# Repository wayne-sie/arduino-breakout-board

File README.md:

# arduino-breakout-board
R3 Hardware project - breakout board interfacing arduino due and adafruit ethernet featherwing 
Designed with EAGLE

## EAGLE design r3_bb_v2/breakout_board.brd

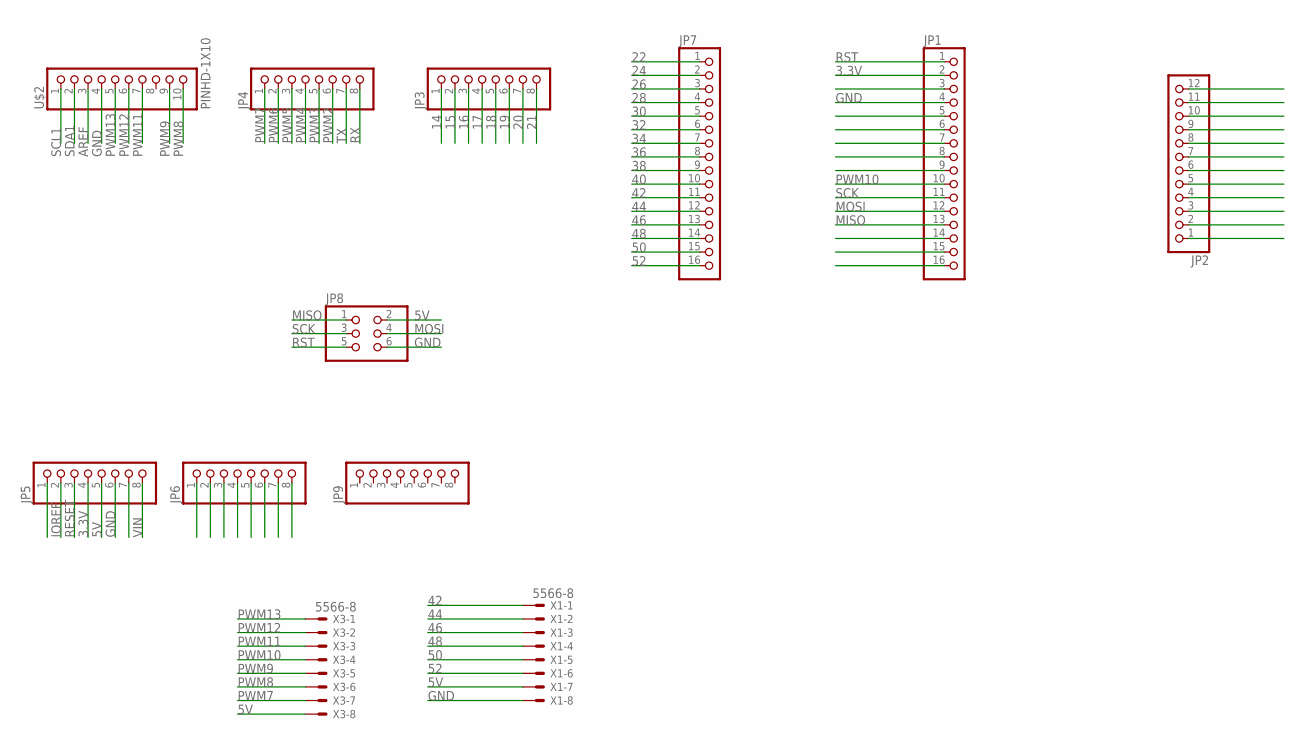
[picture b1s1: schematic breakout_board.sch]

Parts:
JP1, JP7: PINHD-1X16; 1X16
JP2: PINHD-1X12; 1X12
JP3, JP4, JP5, JP6, JP9: PINHD-1X8BIG; 1X08-BIG
JP8: PINHD-2X3; 2X03
U$2: PINHD-1X10; 1X10-BIG
X1, X3: 5566-8

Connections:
3.3V: JP1.2, JP5.4
5V: JP5.5, JP8.2, X1.7, X3.8
14: JP3.1
15: JP3.2
16: JP3.3
17: JP3.4
18: JP3.5
19: JP3.6
20: JP3.7
21: JP3.8
22: JP7.1
24: JP7.2
26: JP7.3
28: JP7.4
30: JP7.5
32: JP7.6
34: JP7.7
36: JP7.8
38: JP7.9
40: JP7.10
42: JP7.11, X1.1
44: JP7.12, X1.2
46: JP7.13, X1.3
48: JP7.14, X1.4
50: JP7.15, X1.5
52: JP7.16, X1.6
AREF: U$2.3
GND: JP1.4, JP5.6, JP8.6, U$2.4, X1.8
IOREF: JP5.2
MISO: JP1.13, JP8.1
MOSI: JP1.12, JP8.4
PWM2: JP4.6
PWM3: JP4.5
PWM4: JP4.4
PWM5: JP4.3
PWM6: JP4.2
PWM7: JP4.1, X3.7
PWM8: U$2.10, X3.6
PWM9: U$2.9, X3.5
PWM10: JP1.10, X3.4
PWM11: U$2.7, X3.3
PWM12: U$2.6, X3.2
PWM13: U$2.5, X3.1
RESET: JP5.3
RST: JP1.1, JP8.5
RX: JP4.8
SCK: JP1.11, JP8.3
SCL1: U$2.1
SDA1: U$2.2
TX: JP4.7
VIN: JP5.8

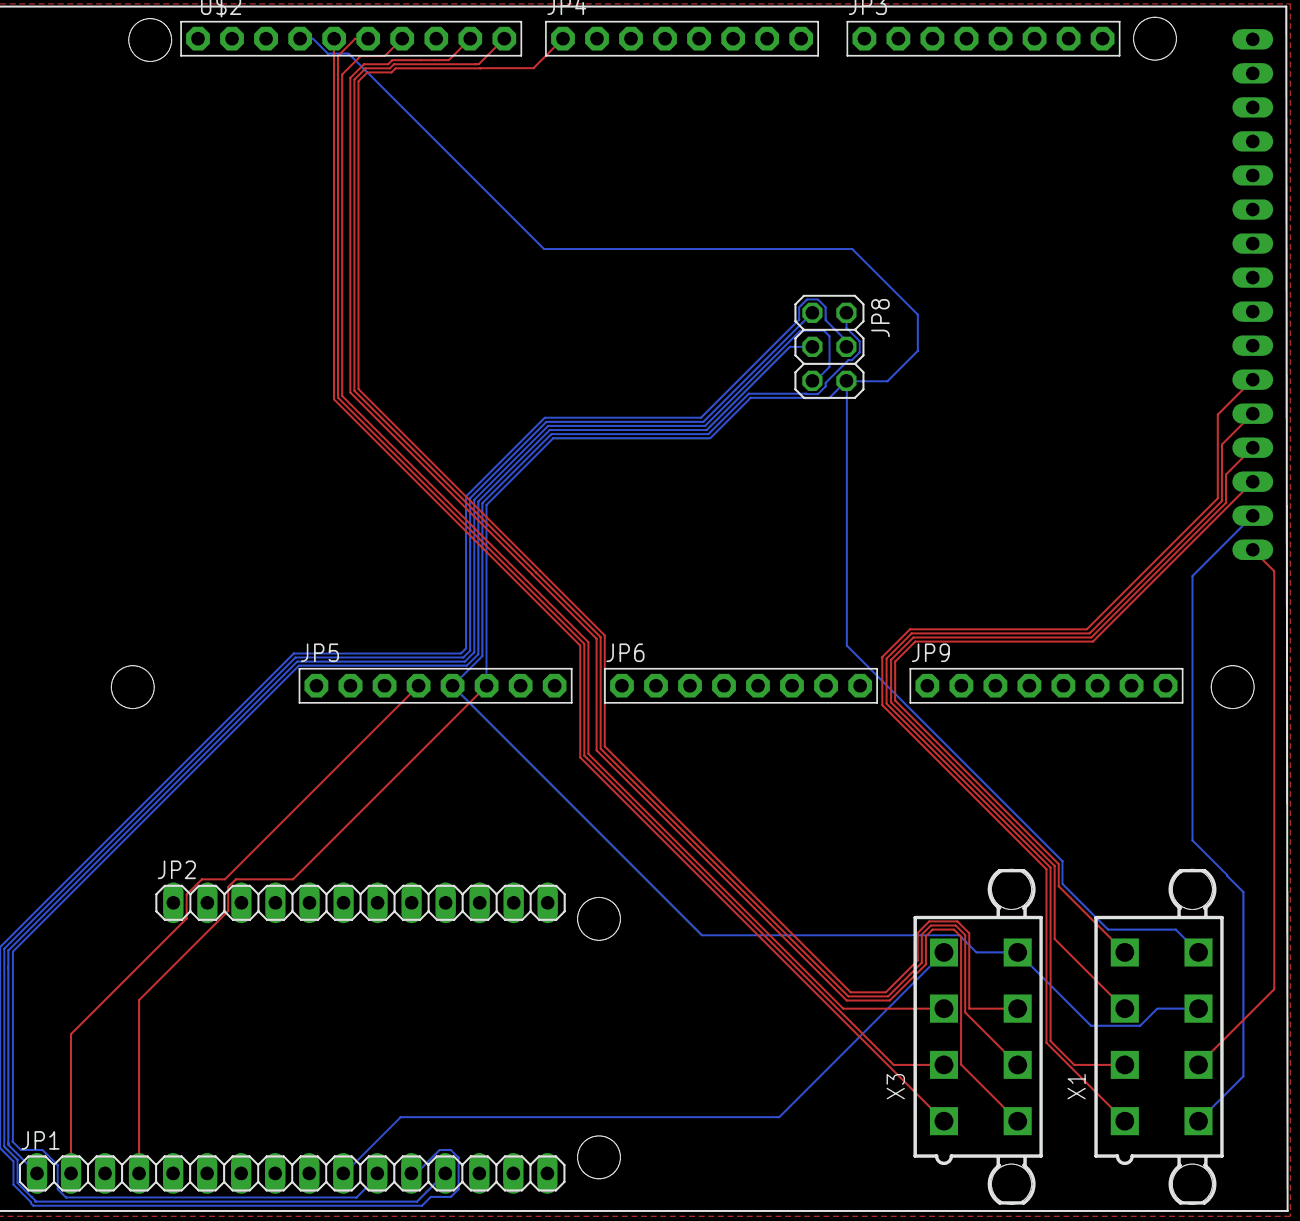
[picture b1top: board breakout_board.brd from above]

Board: 2 copper layers, 12 parts (1 on the bottom side), 20 nets.

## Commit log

2020-08-23 r3 arduino breakout board
